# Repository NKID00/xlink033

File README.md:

# xlink033

Ultra-affordable debug probe built around the 30 cent MCU CH32X033F8P6, featuring:

- Bootstrap select button, so you won't need yet another probe to unbrick the probe itself!
- 5V and 3V3 dual switchable current-limited output
- RVSWD/SDI, JTAG/SWD, UART and RST signal
- Full-speed USB
- Link and activity indicator LED

### License

Hardware part (directory `hw/`) is distributed under CERN-OHL-S-2.0 or any later version.

<sub>
Copyright (C) 2025 NKID00 <br>
This source describes Open Hardware and is licensed under the CERN-OHL-S v2 or any later version. <br>
You may redistribute and modify this source and make products using it under the terms of the CERN-OHL-S v2 (https://ohwr.org/cern_ohl_s_v2.txt). <br>
This source is distributed WITHOUT ANY EXPRESS OR IMPLIED WARRANTY, INCLUDING OF MERCHANTABILITY, SATISFACTORY QUALITY AND FITNESS FOR A PARTICULAR PURPOSE. Please see the CERN-OHL-S v2 for applicable conditions. <br>
As per CERN-OHL-S v2 section 4, should You produce hardware based on this source, You must where practicable maintain the Source Location (https://github.com/NKID00/xlink033) visible on the external case of the Gizmo or other products you make using this source. <br>
</sub><br>

Software part (directory `sw/`) is distributed under GPL-3.0-or-later.

<sub>
Copyright (C) 2025 NKID00 <br>
This program is free software: you can redistribute it and/or modify it under the terms of the GNU General Public License as published by the Free Software Foundation, either version 3 of the License, or (at your option) any later version. <br>
This program is distributed in the hope that it will be useful, but WITHOUT ANY WARRANTY; without even the implied warranty of MERCHANTABILITY or FITNESS FOR A PARTICULAR PURPOSE.  See the GNU General Public License for more details. <br>
You should have received a copy of the GNU General Public License along with this program.  If not, see &le;https://www.gnu.org/licenses/&gt;.
</sub>

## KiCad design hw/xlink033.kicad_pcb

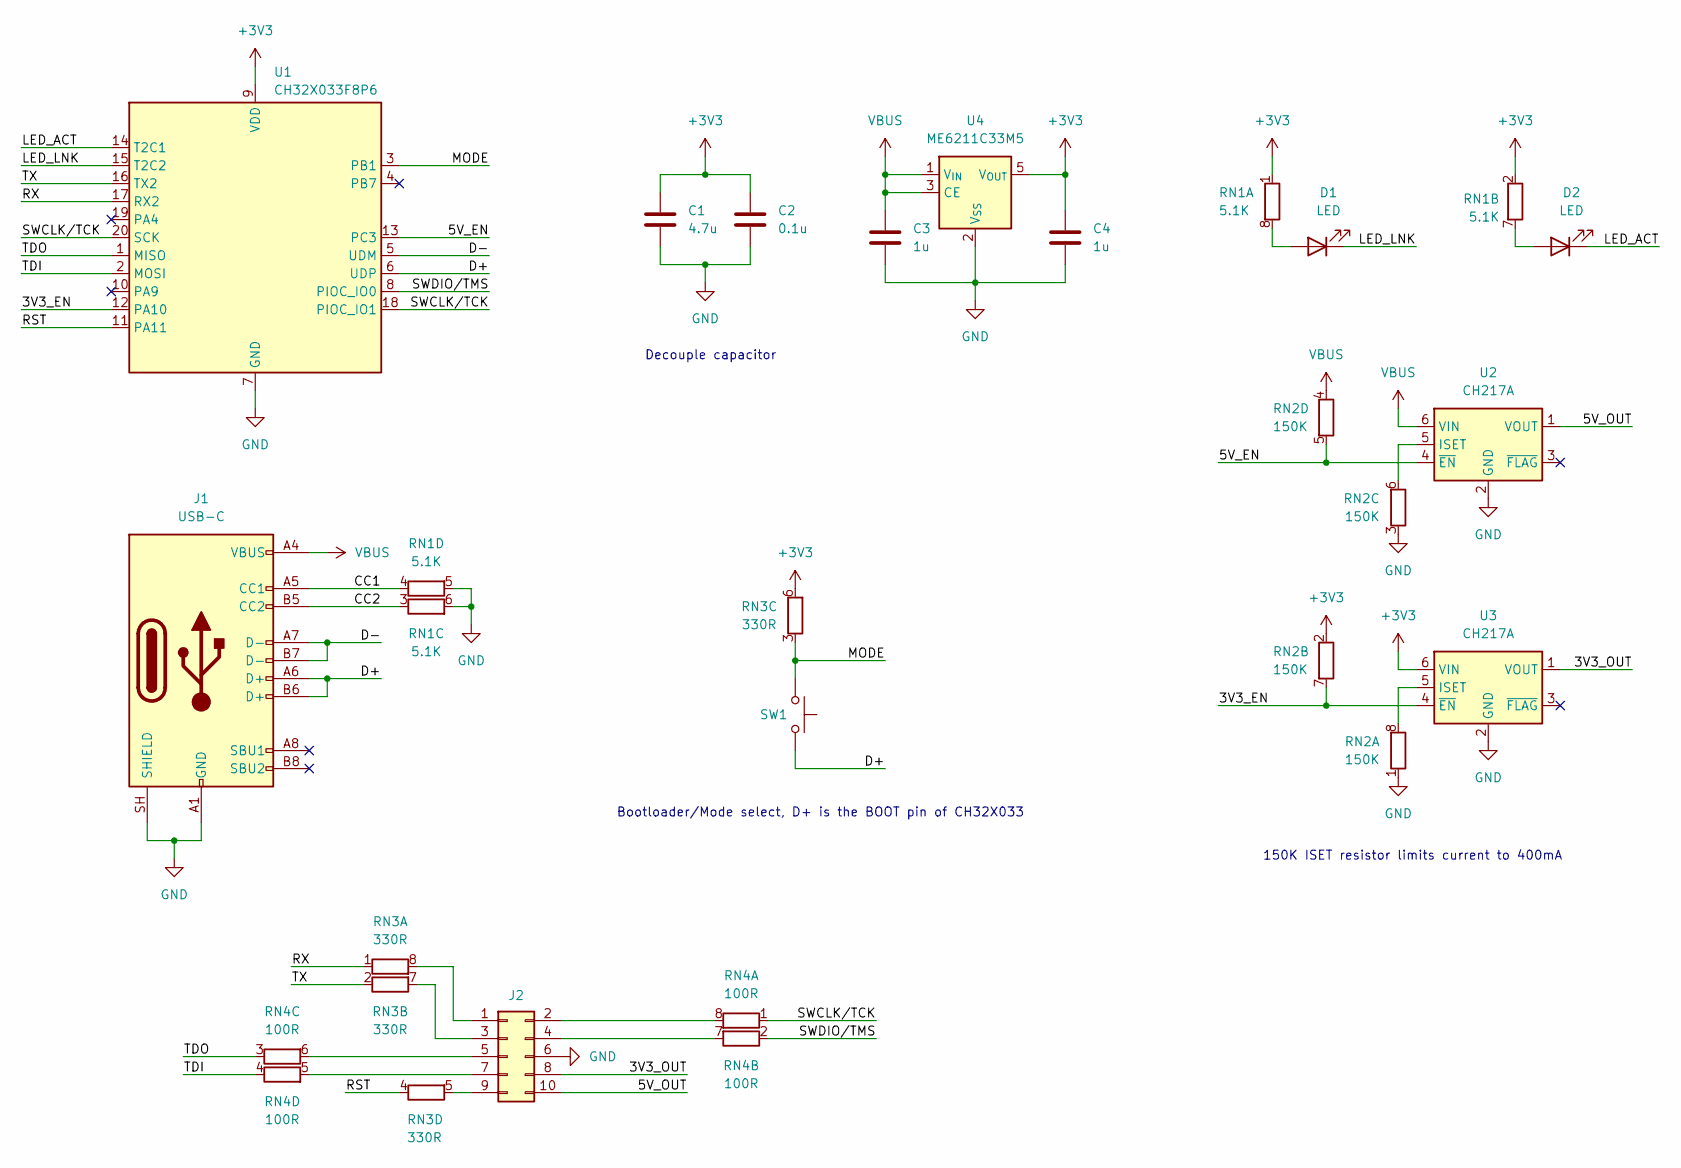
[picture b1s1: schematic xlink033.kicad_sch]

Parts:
C1: 4.7u; C_0603_1608Metric; LCSC C19666
C2: 0.1u; C_0603_1608Metric; LCSC C14663
C3, C4: 1u; C_0603_1608Metric; LCSC C15849
D1: LED; LED_0603_1608Metric; LCSC C84268
D2: LED; LED_0603_1608Metric; LCSC C84269
J1: USB-C; USB_C_Receptacle_GCT_USB4105-xx-A_16P_TopMnt_Horizontal; LCSC C2988369
J2: PinHeader_2x05_P2.54mm_Horizontal
RN1: 5.1K; R_Array_Convex_4x0603; LCSC C12028
RN2: 150K; R_Array_Convex_4x0603; LCSC C57446
RN3: 330R; R_Array_Convex_4x0603; LCSC C12018
RN4: 100R; R_Array_Convex_4x0603; LCSC C25506
SW1: SW_SPST_TS-1088-xR020; LCSC C720477
U1: CH32X033F8P6; TSSOP-20_4.4x6.5mm_P0.65mm; LCSC C54973763
U2, U3: CH217A; SOT-23-6; LCSC C54973763
U4: ME6211C33M5; SOT-23-5; LCSC C54973763

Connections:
+3V3: C1.1, C2.1, C4.1, RN1.1 (R1.1), RN1.2 (R2.1), RN2.2 (R2.1), RN3.6 (R3.2), U1.9 (VDD), U3.6 (VIN), U4.5 (V_{OUT})
/3V3_EN: RN2.7 (R2.2), U1.12 (PA10), U3.4 (~EN)
/3V3_OUT: J2.8, U3.1 (VOUT)
/5V_EN: RN2.5 (R4.2), U1.13 (PC3), U2.4 (~EN)
/5V_OUT: J2.10, U2.1 (VOUT)
/CC1: J1.A5 (CC1), RN1.4 (R4.1)
/CC2: J1.B5 (CC2), RN1.3 (R3.1)
/D+: J1.A6 (D+), J1.B6 (D+), SW1.2, U1.6 (UDP)
/D-: J1.A7 (D-), J1.B7 (D-), U1.5 (UDM)
/LED_ACT: D2.1 (K), U1.14 (T2C1)
/LED_LNK: D1.1 (K), U1.15 (T2C2)
/MODE: RN3.3 (R3.1), SW1.1, U1.3 (PB1)
/RST: RN3.4 (R4.1), U1.11 (PA11)
/RX: RN3.1 (R1.1), U1.17 (RX2)
/SWCLK/TCK: RN4.1 (R1.1), U1.18 (PIOC_IO1), U1.20 (SCK)
/SWDIO/TMS: RN4.2 (R2.1), U1.8 (PIOC_IO0)
/TDI: RN4.4 (R4.1), U1.2 (MOSI)
/TDO: RN4.3 (R3.1), U1.1 (MISO)
/TX: RN3.2 (R2.1), U1.16 (TX2)
GND: C1.2, C2.2, C3.2, C4.2, J1.A1 (GND), J1.A12 (GND), J1.B1 (GND), J1.B12 (GND), J1.SH (SHIELD), J2.6, RN1.5 (R4.2), RN1.6 (R3.2), RN2.1 (R1.1), RN2.3 (R3.1), U1.7 (GND), U2.2 (GND), U3.2 (GND), U4.2 (V_{SS})
unnamed: D1.2 (A), RN1.8 (R1.2)
unnamed: D2.2 (A), RN1.7 (R2.2)
unnamed: J2.1, RN3.8 (R1.2)
unnamed: J2.2, RN4.8 (R1.2)
unnamed: J2.3, RN3.7 (R2.2)
unnamed: J2.4, RN4.7 (R2.2)
unnamed: J2.5, RN4.6 (R3.2)
unnamed: J2.7, RN4.5 (R4.2)
unnamed: J2.9, RN3.5 (R4.2)
unnamed: RN2.8 (R1.2), U3.5 (ISET)
unnamed: RN2.6 (R3.2), U2.5 (ISET)
VBUS: C3.1, J1.A4 (VBUS), J1.A9 (VBUS), J1.B4 (VBUS), J1.B9 (VBUS), RN2.4 (R4.1), U2.6 (VIN), U4.1 (V_{IN}), U4.3 (CE)

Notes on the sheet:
Bootloader/Mode select, D+ is the BOOT pin of CH32X033
150K ISET resistor limits current to 400mA
Decouple capacitor

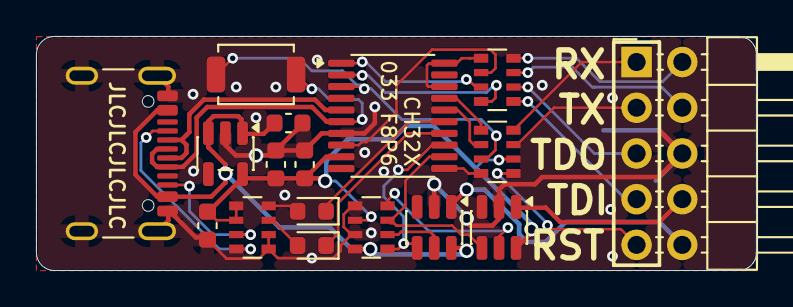
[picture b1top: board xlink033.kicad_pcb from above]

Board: 2 copper layers, 40.0 x 13.0 mm, 17 parts (0 on the bottom side), 32 nets.

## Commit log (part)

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2025-11-23 feat: init
2025-11-24 feat: add pdf
